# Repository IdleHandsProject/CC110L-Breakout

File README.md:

CC110L-Breakout
===============

Breakoutboard for the CC110L RF chip

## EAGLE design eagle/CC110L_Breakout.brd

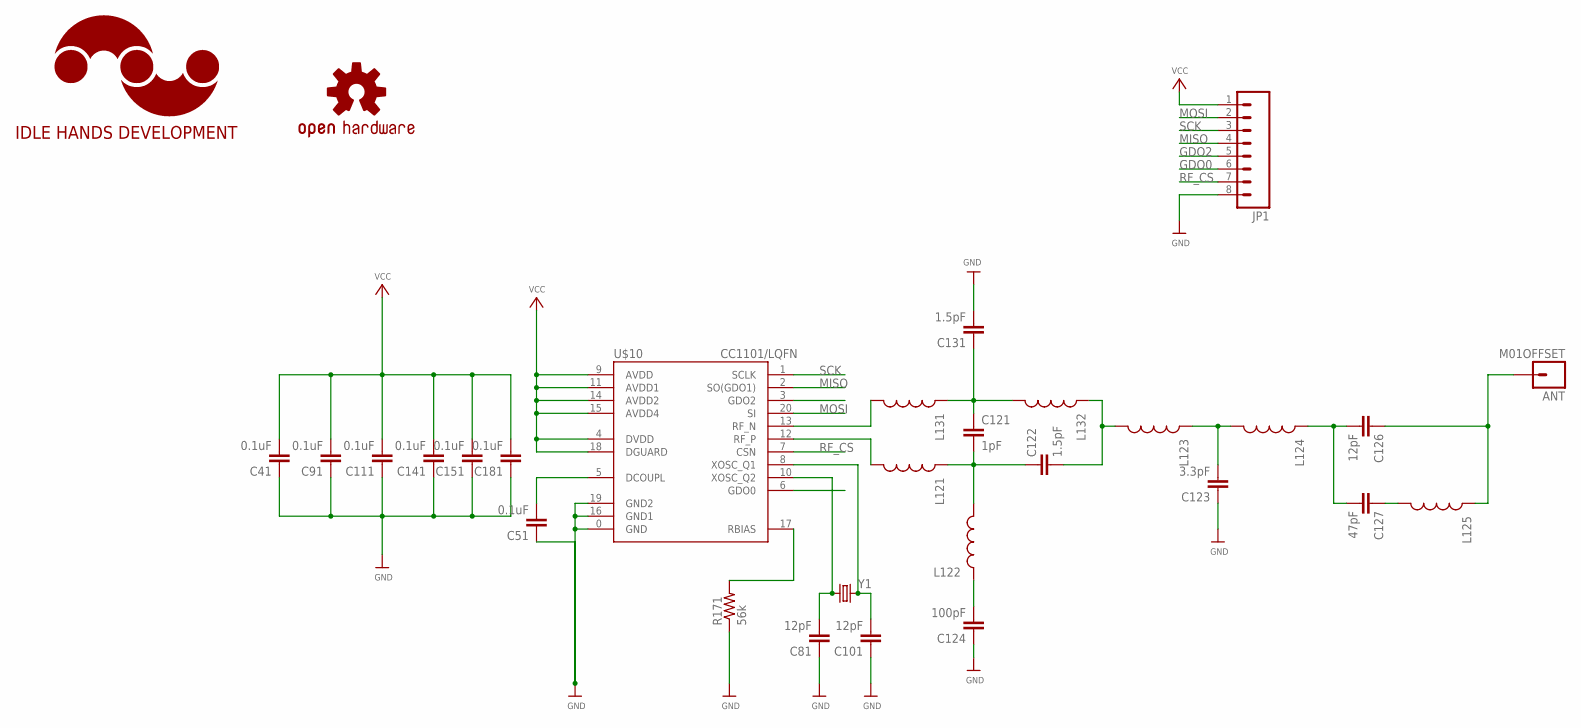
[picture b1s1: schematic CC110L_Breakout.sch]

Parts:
ANT: M01OFFSET; 1X01_OFFSET
C41, C51, C91, C111, C141, C151, C181: 0.1uF; C0402
C81, C101, C126: 12pF; C0402
C121: 1pF; C0402
C122, C131: 1.5pF; C0402
C123: 3.3pF; C0402
C124: 100pF; C0402
C127: 47pF; C0402
JP1: M08LOCK; 1X08_LOCK
L121, L122, L123, L124, L125, L131, L132: INDUCTOR0402; C0402
LOGO1: OSHW-LOGOS; OSHW-LOGO-S
LOGO2: IDLEHANDS_LOGOS; IHD-LOGO-S
R171: 56k; R0402
U$10: CC1101/LQFN; QFN20
Y1: CRYSTAL3.2X2.5; CRYSTAL-SMD-3.2X2.5

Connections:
GDO0: JP1.6, U$10.6 (GDO0)
GDO2: JP1.5, U$10.3 (GDO2)
GND: C41.1, C51.1, C81.1, C91.1, C101.1, C111.1, C123.1, C124.1, C131.2, C141.1, C151.1, C181.1, JP1.8, R171.1, U$10.0 (GND), U$10.16 (GND1), U$10.19 (GND2)
MISO: JP1.4, U$10.2 (SO(GDO1))
MOSI: JP1.2, U$10.20 (SI)
unnamed: L131.2, U$10.13 (RF_N)
unnamed: C121.1, C131.1, L131.1, L132.2
unnamed: L121.2, U$10.12 (RF_P)
unnamed: C121.2, C122.1, L121.1, L122.2
unnamed: C124.2, L122.1
unnamed: C122.2, L123.2, L132.1
unnamed: C123.2, L123.1, L124.2
unnamed: C126.2, C127.2, L124.1
unnamed: C127.1, L125.2
unnamed: ANT.1, C126.1, L125.1
unnamed: C101.2, U$10.8 (XOSC_Q1), Y1.3 (2)
unnamed: C81.2, U$10.10 (XOSC_Q2), Y1.1
unnamed: C51.2, U$10.5 (DCOUPL)
unnamed: R171.2, U$10.17 (RBIAS)
RF_CS: JP1.7, U$10.7 (CSN)
SCK: JP1.3, U$10.1 (SCLK)
VCC: C41.2, C91.2, C111.2, C141.2, C151.2, C181.2, JP1.1, U$10.4 (DVDD), U$10.9 (AVDD), U$10.11 (AVDD1), U$10.14 (AVDD2), U$10.15 (AVDD4), U$10.18 (DGUARD)

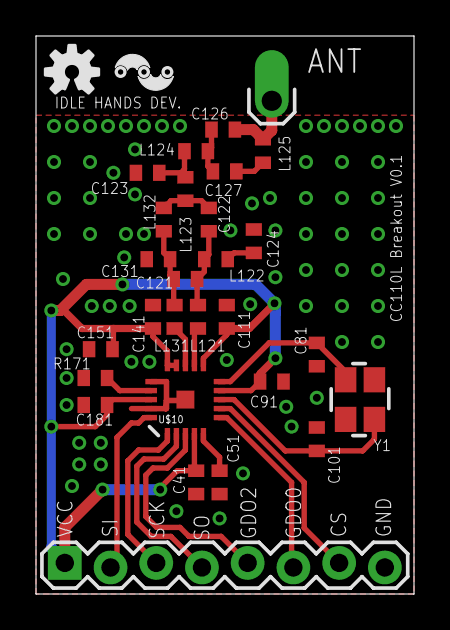
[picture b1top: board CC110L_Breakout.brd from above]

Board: 2 copper layers, 21.0 x 31.0 mm, 30 parts (0 on the bottom side), 22 nets.

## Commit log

2014-08-15 almost completed board
2014-08-17 Finilized and uploaded to OSHpark ordered

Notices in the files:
parts and their libraries:
SparkFun-Connectors: Licensing: CC v3.0 Share-Alike You are welcome to use this library for commercial purposes.
